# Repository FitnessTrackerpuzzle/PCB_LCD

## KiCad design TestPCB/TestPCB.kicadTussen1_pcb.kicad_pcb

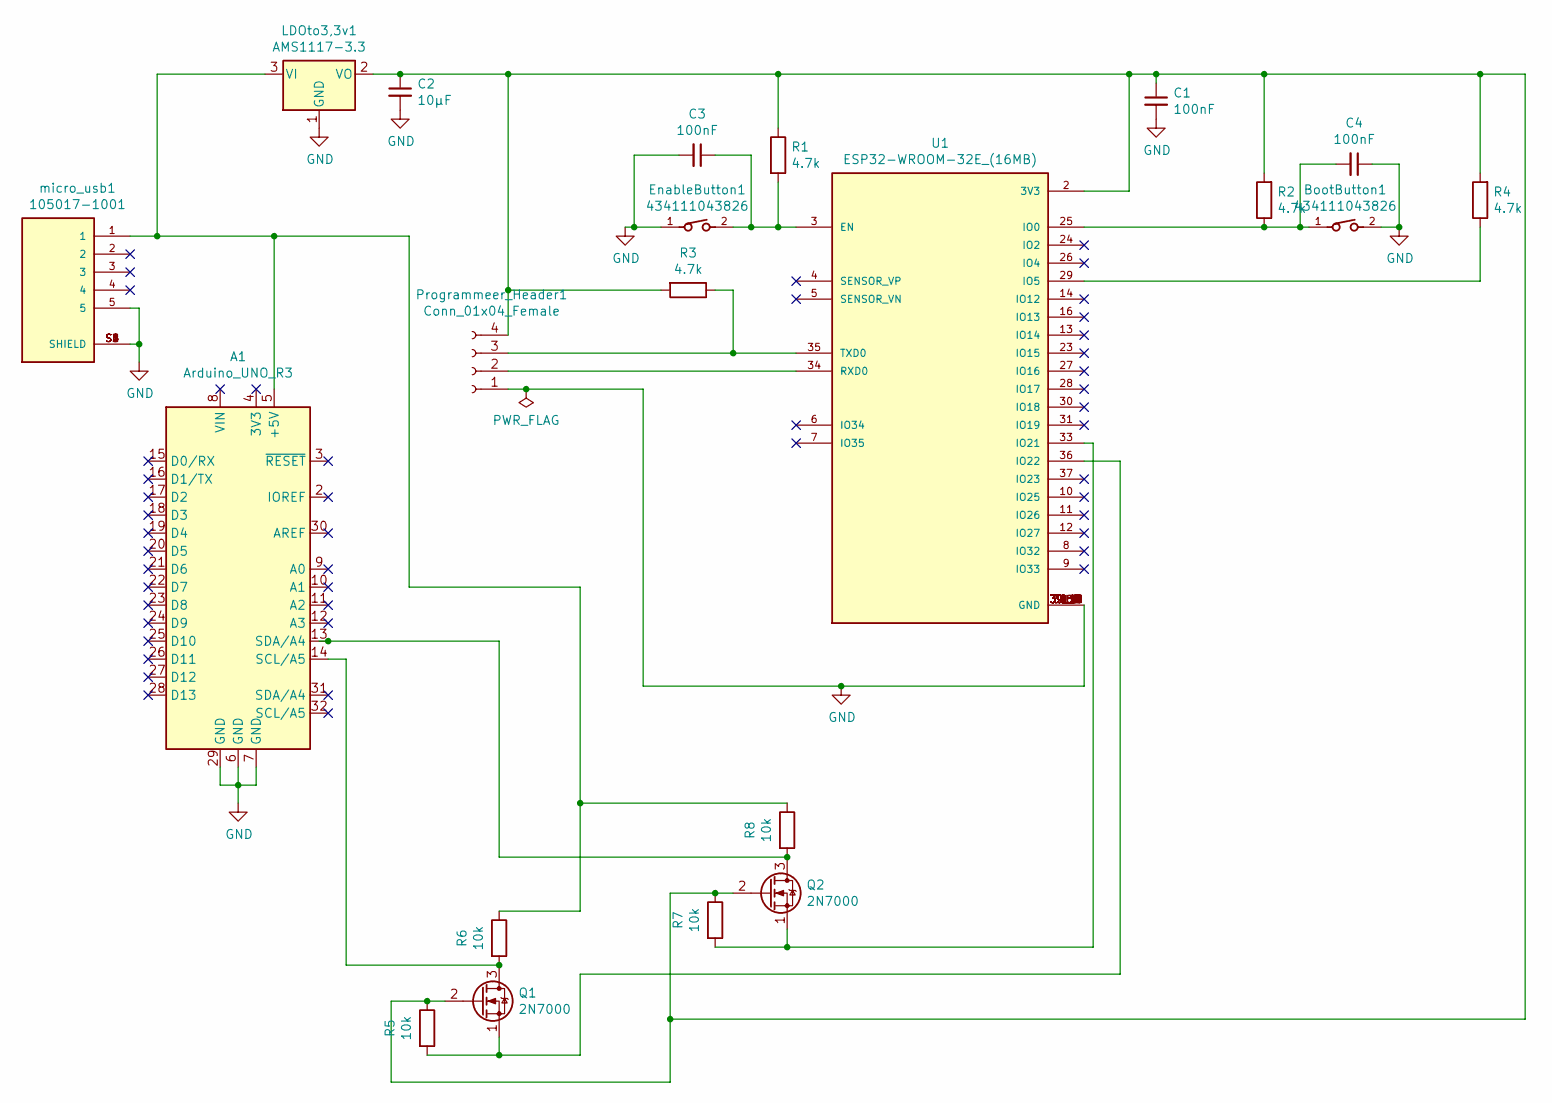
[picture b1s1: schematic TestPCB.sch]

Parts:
A1: Arduino_UNO_R3
BootButton1: 434111043826
C1, C3, C4: 100nF; C_1206_3216Metric
C2: 10µF; C_1206_3216Metric
EnableButton1: 434111043826
LDOto3,3v1: AMS1117-3.3; SOT-223-3_TabPin2
Programmeer_Header1: Conn_01x04_Female; NS-Tech_Grove_1x04_P2mm_Vertical
Q1, Q2: 2N7000; SOT23-3
R1, R2, R3, R4: 4.7k; R_1206_3216Metric
R5, R6, R7, R8: 10k; R_1206_3216Metric
U1: ESP32-WROOM-32E_(16MB); MODULE_ESP32-WROOM-32E_(16MB); PARTREV 1.1
micro_usb1: 105017-1001; MOLEX_105017-1001; PARTREV F

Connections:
GND: A1.6 (GND), A1.7 (GND), A1.29 (GND), BootButton1.2, C1.2, C2.2, C3.2, C4.1, EnableButton1.1, LDOto3,3v1.1 (GND), Programmeer_Header1.1, U1.1 (GND), U1.15 (GND), U1.38 (GND), U1.39_1 (GND), U1.39_2 (GND), U1.39_3 (GND), U1.39_4 (GND), U1.39_5 (GND), U1.39_6 (GND), U1.39_7 (GND), U1.39_8 (GND), U1.39_9 (GND), U1.39_10 (GND), U1.39_11 (GND), U1.39_12 (GND), U1.39_13 (GND), U1.39_14 (GND), U1.39_15 (GND), U1.39_16 (GND), U1.39_17 (GND), U1.39_18 (GND), U1.39_19 (GND), U1.39_20 (GND), U1.39_21 (GND), micro_usb1.5, micro_usb1.S1 (SHIELD), micro_usb1.S2 (SHIELD), micro_usb1.S3 (SHIELD), micro_usb1.S4 (SHIELD), micro_usb1.S5 (SHIELD), micro_usb1.S6 (SHIELD)
unnamed: A1.5 (+5V), LDOto3,3v1.3 (VI), R6.1, R8.1, micro_usb1.1
unnamed: A1.13 (SDA/A4), Q2.3 (D), R8.2
unnamed: A1.14 (SCL/A5), Q1.3 (D), R6.2
unnamed: BootButton1.1, C4.2, R2.1, U1.25 (IO0)
unnamed: C1.1, C2.1, LDOto3,3v1.2 (VO), Programmeer_Header1.4, Q1.2 (G), Q2.2 (G), R1.1, R2.2, R3.2, R4.2, R5.1, R7.1, U1.2 (3V3)
unnamed: C3.1, EnableButton1.2, R1.2, U1.3 (EN)
unnamed 33: micro_usb1.2; also elsewhere on the board
unnamed 34: micro_usb1.3; also elsewhere on the board
unnamed: Programmeer_Header1.2, U1.34 (RXD0)
unnamed: Programmeer_Header1.3, R3.1, U1.35 (TXD0)
unnamed: Q1.1 (S), R5.2, U1.36 (IO22)
unnamed: Q2.1 (S), R7.2, U1.33 (IO21)
unnamed: R4.1, U1.29 (IO5)

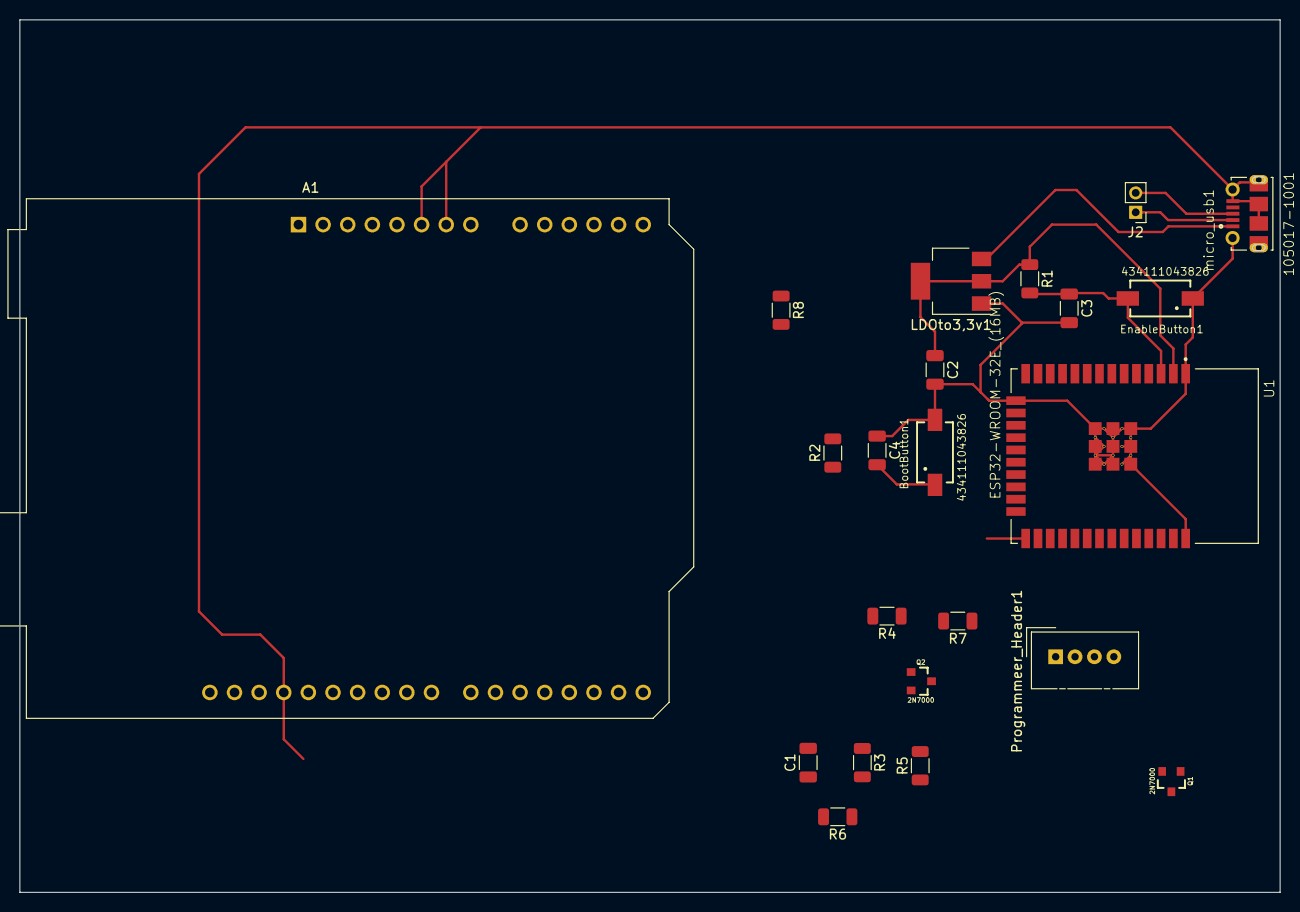
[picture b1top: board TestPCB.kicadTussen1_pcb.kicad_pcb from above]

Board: 2 copper layers, 130.0 x 90.0 mm, 22 parts (0 on the bottom side), 14 nets.

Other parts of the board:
J2: Conn_01x02_Female; PinHeader_1x02_P2.00mm_Vertical

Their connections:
unnamed 33: J2.1; also elsewhere on the board
unnamed 34: J2.2; also elsewhere on the board
